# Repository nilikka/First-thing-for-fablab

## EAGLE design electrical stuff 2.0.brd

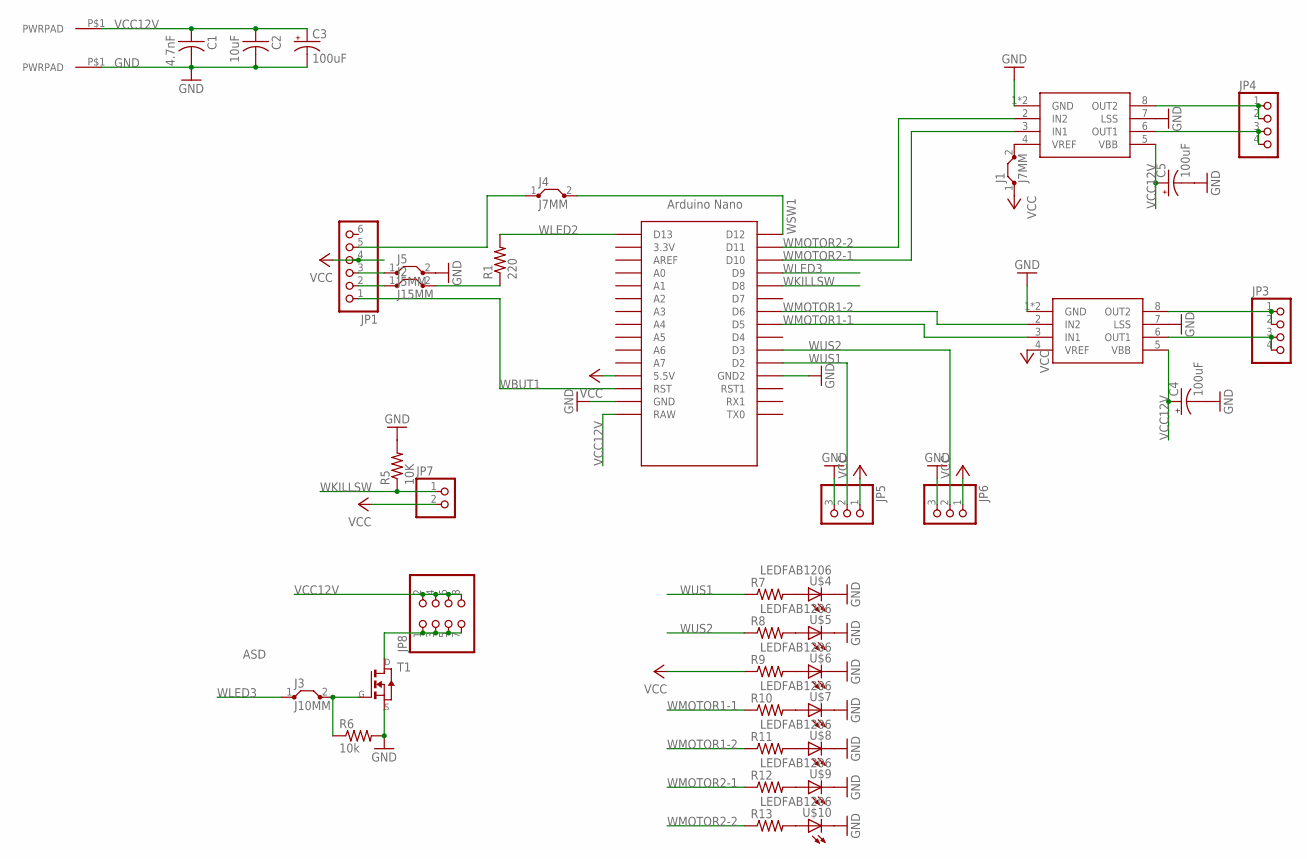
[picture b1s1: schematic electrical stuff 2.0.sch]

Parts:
C1: 4.7nF; C1206FAB
C2: 10uF; C1206FAB
C3, C4, C5: 100uF; CPOL-RADIAL-2.5MM-6.5MM
GND: PWRPAD2-5MM; PWRPAD_2-5MM
J1, J4: J7MM; 07
J2: J15MM; 15
J3: J10MM; 10
J5: J5MM; 05
JP1: PINHD-1X6; 1X06
JP3, JP4: PINHD-1X4; 1X04
JP5, JP6: PINHD-1X3; 1X03
JP7: PINHD-1X2; 1X02
JP8: PINHD-2X4; 2X04
R1: 220; R1206FAB
R5: 10K; R1206FAB
R6: 10k; R1206FAB
R7, R8, R9, R10, R11, R12, R13: RES-US1206FAB; R1206FAB
T1: NMOSFETTO252; TO252
U$1: NANO
U$2, U$3: A4953; SOIC8_PAD
U$4, U$5, U$6, U$7, U$8, U$9, U$10: LEDFAB1206; LED1206FAB
VCC12V: VCC12V; PWRPAD_2-5MM

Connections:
ASD: J3.2, R6.1, T1.1 (G)
GND: C1.2, C2.2, C3.2 (-), C4.2 (-), C5.2 (-), GND.P$1, J5.2, JP5.3, JP6.3, R5.2, R6.2, T1.2 (S), U$1.GND, U$1.GND1 (GND2), U$2.1 (GND), U$2.7 (LSS), U$2.GND, U$3.1 (GND), U$3.7 (LSS), U$3.GND, U$4.2 (C), U$5.2 (C), U$6.2 (C), U$7.2 (C), U$8.2 (C), U$9.2 (C), U$10.2 (C)
unnamed: J5.1, JP1.3
unnamed: JP8.1, JP8.3, JP8.5, JP8.7, T1.3 (D)
unnamed: JP4.3, JP4.4, U$3.6 (OUT1)
unnamed: J2.2, R1.1
unnamed: JP4.1, JP4.2, U$3.8 (OUT2)
unnamed: JP3.1, JP3.2, U$2.8 (OUT2)
unnamed: JP3.3, JP3.4, U$2.6 (OUT1)
unnamed: J1.2, U$3.4 (VREF)
unnamed: J2.1, JP1.2
unnamed: R7.2, U$4.1 (A)
unnamed: J4.1, JP1.5
unnamed: R8.2, U$5.1 (A)
unnamed: R9.2, U$6.1 (A)
unnamed: R10.2, U$7.1 (A)
unnamed: R11.2, U$8.1 (A)
unnamed: R12.2, U$9.1 (A)
unnamed: R13.2, U$10.1 (A)
VCC: J1.1, JP1.4, JP5.1, JP6.1, JP7.2, R9.1, U$1.5V (5.5V), U$2.4 (VREF)
VCC12V: C1.1, C2.1, C3.1 (+), C4.1 (+), C5.1 (+), JP8.2, JP8.4, JP8.6, JP8.8, U$1.RAW, U$2.5 (VBB), U$3.5 (VBB), VCC12V.P$1
WBUT1: JP1.1, U$1.RST
WKILLSW: JP7.1, R5.1, U$1.D8
WLED2: R1.2, U$1.D13
WLED3: J3.1, U$1.D9
WMOTOR1-1: R10.1, U$1.D5, U$2.3 (IN1)
WMOTOR1-2: R11.1, U$1.D6, U$2.2 (IN2)
WMOTOR2-1: R12.1, U$1.D10, U$3.3 (IN1)
WMOTOR2-2: R13.1, U$1.D11, U$3.2 (IN2)
WSW1: J4.2, U$1.D12
WUS1: JP5.2, R7.1, U$1.D2
WUS2: JP6.2, R8.1, U$1.D3

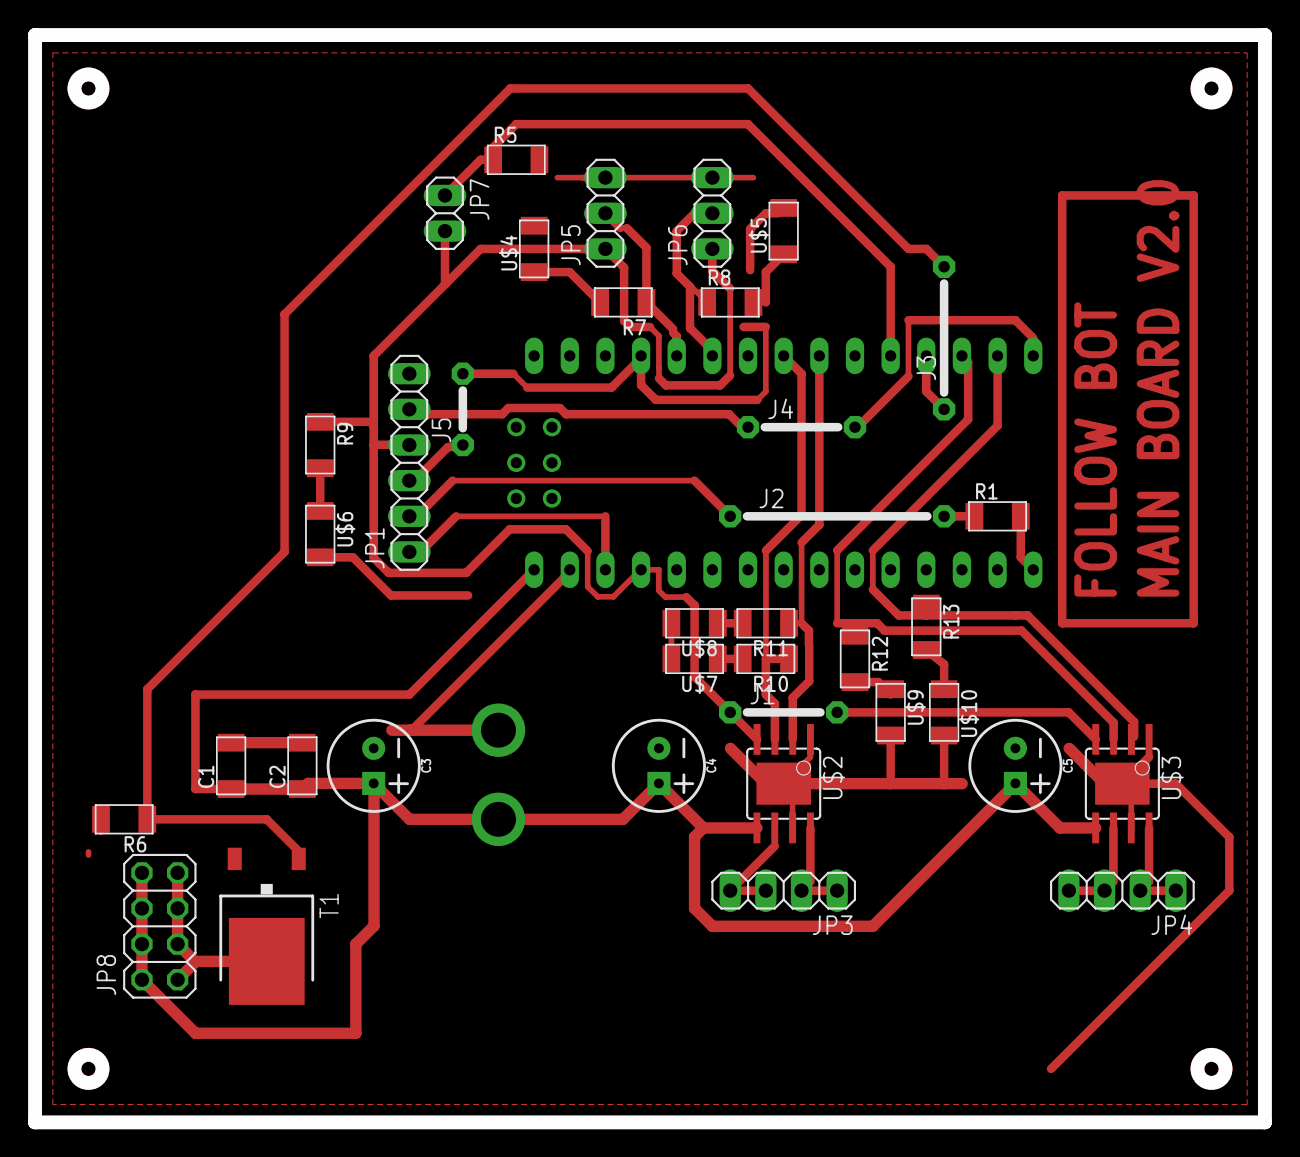
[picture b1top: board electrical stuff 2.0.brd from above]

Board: 2 copper layers, 87.6 x 77.5 mm, 40 parts (1 on the bottom side), 32 nets.

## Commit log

2018-08-17 Add eagle files
2018-08-17 Add pinlist

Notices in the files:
parts and their libraries:
SparkFun-Capacitors: Licensing: Creative Commons ShareAlike 4.0 International - https://creativecommons.org/licenses/by-sa/4.0
